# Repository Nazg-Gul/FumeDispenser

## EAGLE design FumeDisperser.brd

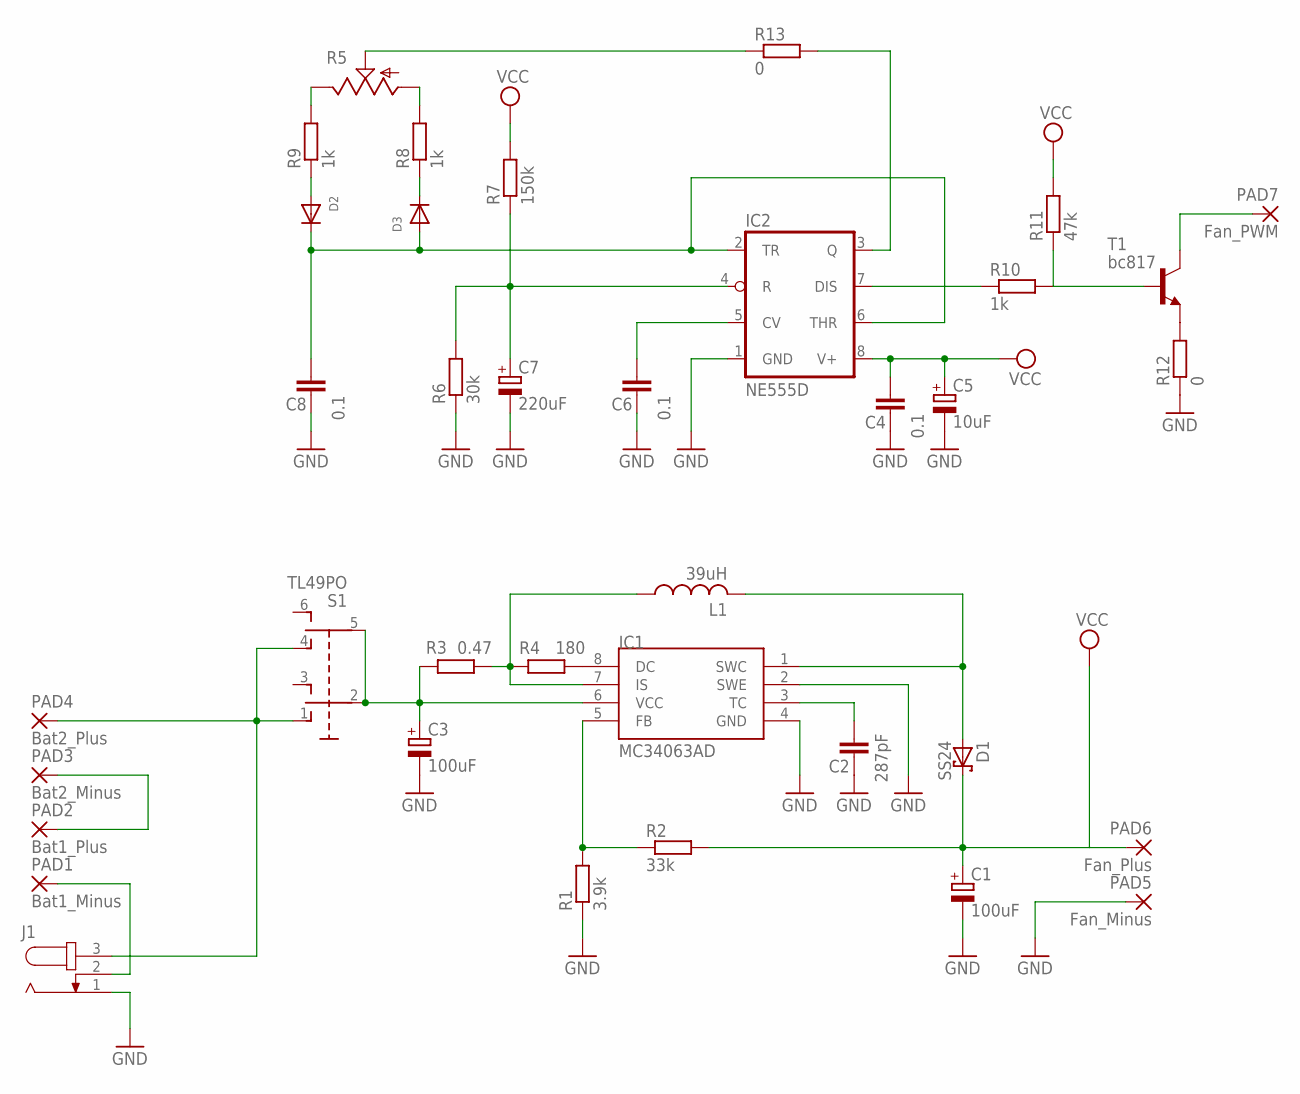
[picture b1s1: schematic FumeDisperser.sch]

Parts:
C1, C3: 100uF; D/7343-31R
C2: 287pF; C1206
C4, C6, C8: 0.1; C1206
C5: 10uF; D/7343-31R
C7: 220uF; D/7343-31R
D1: SS24; SMB
D2, D3: DIODESOD-123; SOD-123
IC1: MC34063AD; SOIC8
IC2: NE555D; SO08
J1: JACK-PLUG0; SPC4077
L1: 39uH; L3225P
PAD1: Bat1_Minus; SMD2,54-5,08
PAD2: Bat1_Plus; SMD2,54-5,08
PAD3: Bat2_Minus; SMD2,54-5,08
PAD4: Bat2_Plus; SMD2,54-5,08
PAD5: Fan_Minus; SMD2,54-5,08
PAD6: Fan_Plus; SMD2,54-5,08
PAD7: Fan_PWM; SMD2,54-5,08
R1: 3.9k; M1206
R2: 33k; M1206
R3: 0.47; M1206
R4: 180; M1206
R5: US-EVUF2A; EVUF
R6: 30k; M1206
R7: 150k; M1206
R8, R9, R10: 1k; M1206
R11: 47k; M1206
R12, R13: 0; M1206
S1: TL49PO; TL4XPO
T1: bc817; SOT23-BEC

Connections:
GND: C1.-, C2.2, C3.-, C4.2, C5.-, C6.2, C7.-, C8.2, IC1.2 (SWE), IC1.4 (GND), IC2.1 (GND), J1.1, PAD5.1, R1.1, R6.1, R12.1
unnamed: D1.A, IC1.1 (SWC), L1.2
unnamed: C6.1, IC2.5 (CV)
unnamed: IC1.5 (FB), R1.2, R2.1
unnamed: C3.+, IC1.6 (VCC), R3.2, S1.2, S1.5 (P1)
unnamed: IC1.7 (IS), L1.1, R3.1, R4.1
unnamed: IC1.8 (DC), R4.2
unnamed: C2.1, IC1.3 (TC)
unnamed: PAD2.1, PAD3.1
unnamed: J1.3, PAD4.1, S1.1 (O), S1.4 (O1)
unnamed: C8.1, D2.C, D3.A, IC2.2 (TR), IC2.6 (THR)
unnamed: J1.2, PAD1.1
unnamed: R5.2 (S), R13.1
unnamed: C7.+, IC2.4 (R), R6.2, R7.1
unnamed: D3.C, R8.1
unnamed: D2.A, R9.1
unnamed: R5.3 (E), R9.2
unnamed: R5.1 (A), R8.2
unnamed: IC2.3 (Q), R13.2
unnamed: IC2.7 (DIS), R10.1
unnamed: R10.2, R11.1, T1.B
unnamed: PAD7.1, T1.C
unnamed: R12.2, T1.E
VCC: C1.+, C4.1, C5.+, D1.C, IC2.8 (V+), PAD6.1, R2.2, R7.2, R11.2

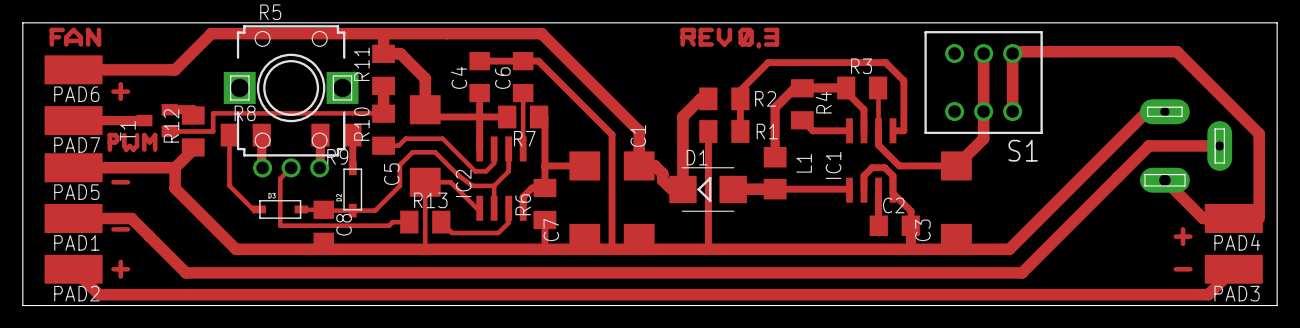
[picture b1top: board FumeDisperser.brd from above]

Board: 2 copper layers, 109.8 x 24.8 mm, 37 parts (1 on the bottom side), 24 nets.

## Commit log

2017-06-16 Add PWM controller circuit
